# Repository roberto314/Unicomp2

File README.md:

# UNICOMP #

A modular 8-bit Computer able to recreate (nearly) every microcomputer of the mid 70s to early 80s 
in Hardware without FPGAs (although an FPGA can be added). Can also be used as a teaching tool for:

* VHDL or Verilog
* C
* RTOS (STM32F401 runs ChibiOS Link: https://www.chibios.org)
* Python
* bash and linux in general (Olimex board runs linux with fbterm and tmux)
* Harwaredesign
* Timing of CPUs
* maybe Assembler
* SPI and I2C Interfaces
* CPLDs and FPGAs

It is different from other designs because of these points:

* it uses a 3.3V only Bus,
* it uses fast RAM for chipselect with two byte resolution over the whole 1MB range,
* it uses one SRAM for RAM and ROM replacement (can be write writeprotected) with 512kB (1MB possible),
* it uses a clock generator chip (DS1085) - no more crystals to change,
* it is configureable via STM32 (RAM and ROM content, Clock frequency, chip select lines),
* it can program the CPLDs (only XC9572 and XC9536 tested) from the olimex board - no external programmer and no cables to connect,
* Board size is 100mm x 100mm - no backplane (like the PC/104 standard. Link: https://en.wikipedia.org/wiki/PC/104).
* and maybe most convenient: it can change RAM and ROM content on the fly without crashing the CPU. 
  For example starting the Apple I, going into Basic and uploading the program in about half a second is really nice.

Version 2.00

Unicomp plus Logic Analyzer:

### Unicomp modules ###

* Input board:
	- a simple board to connect the signals to a linux SBC like a Raspberry Pi or an Olimex A20
	- also generates the main clock with a DS1085 chip (in v2 this will be moved to the RAMROM board).
	- no CPLD

* CPU board:
	- can be any 8-bit CPU (6502, 6802, 6809, 68008, 6803, 8051,...)
	- a CPLD (XC9572) for clock generation and glue logic

6502 Board:

* Multi Serial boaŕd:
	- suggested chip select #0
	- two chip selects on board (second one not connected, but broken out)
	- can be used with the following serial interface chips: MC6850, MOS6551, MOS6552 or pin compatible
	- SRAM for address decoding

Multi Serial Board:

* Multi Parallel boaŕd:
	- suggested chip select #1
	- two chip selects on board
	- can be used with the following parallel interface chips: MC6820, MC6821, MOS6520, MOS6521, MOS6522, MOS6526, MOS8520, MOS6532 in the first slot
    - the first slot can additionally mimic a MOS6530
	- the second slot can accommodate a MOS6522 or pin compatible
    - SRAM for address decoding

* RAMROM board:
	- chip select fixed at #14 (for chipselect RAM) and #15 (rom content)
	- 512k of SRAM plus an extra RAM for address decoding
	- a STM32F401 'blackpill' board to fill the SRAMs with data over USB port from the SBC
	- USB shell on the STM32 to change ROM content on the fly
	- also configures the Address Range of all peripheral modules

* Prototype board:
	- empty board for prototyping
	- no CPLD
    - SRAM for address decoding

* MAX-II (EPM240) board:
	- CPLD plus Buffers

* self made module:
	- chip select can be any non-used line in the Range from 0 to 13.
	- size is 100mm x 100mm
	- there is the prototype board in the repository for the position of the connectors and also the labels (pinout)

### Configuration RAM ###

The configuration is done with 128kx8 fast ram on the peripheral boards. These will be configured from the STM32F401.
One bit is for one Output (of which there are two) and for two addresses (resolution for chipselect is 2 bytes).
The cs = 15 is for writing the main RAM, cs = 14 is the chip select for the RAMROM board.
The rest is free. With two chip select lines per board these are 28 lines.
One byte in the mapping ram has the following format:

| 7    | 6    | 5    | 4    | 3    | 2    | 1    | 0    | Bits       |
|------|------|------|------|------|------|------|------|------------|
| 7,6  | 5,4  | 3,2  | 1,0  | 7,6  | 5,4  | 3,2  | 1,0  | Address    |
| /CS0 | /CS0 | /CS0 | /CS0 | /CS1 | /CS1 | /CS1 | /CS1 | Peripheral |
| /CS  | /CS  | /CS  | /CS  | WP   | WP   | WP   | WP   | RAMROM     |

So 128k are good for 128kx8 Bytes of Addressspace (=1MByte)
The data gets transferred to the STM32 in compact form. Only the Start address, the chipselect and the bitmask (which is Low-active) for every addresses where someting changes are transferred.
A 0xFE for a bitmask means Peripheral chipselect /CS1 is active for two addresses. If the board is the RAMROM board the low nibble is Writeprotect (Hi-active).

A simple configuration block looks líke this:

    (RAM: 0-9FFF, ACIA0: A000-A001, ACIA1: A010-A011, ROM: C000-FFFF)

    00 00 00 0E 00  :  RAM
    00 A0 00 00 EF  :  ACIA0
    00 A0 02 FF FF  :  HOLE
    00 A0 10 00 FE  :  ACIA1
    00 A0 12 FF FF  :  HOLE
    00 C0 00 0E 0F  :  ROM
    01 00 00 FF FF  :  END
    00 00 00        :  noting further

### Working Recreations of old computers ###

| Name                     | prim. IO    | chips used                    | os                               | weblink                                                                 |
|--------------------------|-------------|-------------------------------|----------------------------------|-------------------------------------------------------------------------|
| Grant Searle 6502 board  | serial      | MOS6502, MC6850               | OSI Basic                        |Link: http://searle.x10host.com/6502/Simple6502.html                     |
| Daryl Rictor 6502 board  | serial      | MOS6502, R6551                | SBC-2 (monitor only)             |Link: https://sbc.rictor.org/info2.html                                  |
| Daryl Rictor 6502 board  | serial      | MOS6502, MC6850               | SBC-2 (monitor only)             |Link: https://sbc.rictor.org/info2.html                                  |
| SYM1                     | serial      | MOS6502, UM6532               | SYM1 ( +BASIC +RAE)              |Link: http://retro.hansotten.nl/6502-sbc/synertek-sym-ktm/sym-1/         |
| KIM1                     | serial      | MOS6502, UM6532               | KIM1                             |Link: http://retro.hansotten.nl/6502-sbc/kim-1-manuals-and-software/     |
| Apple I                  | serial      | MOS6502, MĆ6821 (plus Arduino)| Wozmon + BASIC                   |Link: http://retro.hansotten.nl/6502-sbc/apple-1/                        |
| Motorola MEK D2          | serial      | MC6802, MĆ6850                | newbug, xswtbug, mondeb          |Link: https://www.retrotechnology.com/restore/smithbug.html              |
| Motorola MEK D1          | serial      | MC6802, MĆ6821 (plus Arduino) | Mikbug                           |Link: https://www.retrotechnology.com/restore/smithbug.html              |
| Heathkit ET3400          | serial      | MC6802, MĆ6850                | MITS BASIC, TSC MicroBASIC,...   |Link: https://github.com/jefftranter                                     |
| SWTPC 6800               | serial      | MC6802, MĆ6821 (plus Arduino) | Mikbug                           |Link: https://deramp.com/swtpc.com/                                      |
| SWTPC 6800               | serial      | MC6802, MĆ6850                | SWTBUG, SWTBUGA, Mondeb, xSWTBUG |Link: https://deramp.com/swtpc.com/                                      |
| DREAM 6800               | BAS (Video) | MC6802, MAX-II                | DREAM operating System (Chip8)   |Link: http://www.mjbauer.biz/DREAM6800.htm                               |
| HD6303 Board (Eric Klaus)| serial      | HD6303                        | Monitor +BASIC                   |Link: https://sites.google.com/site/ericmklaus/projects-1/hd6303cpuboard |
| MC3 Computer             | serial      | HD6303                        | Monitor                          |Link: https://www.waveguide.se/?article=mc3-a-diy-8-bit-computer         |
| Psion Organizer I        | LCD         | HD6303                        | Psion OS                         |Link: https://www.jaapsch.net/psion/index.htm                            |

### linux single board computer (SBC) ###

I uses an olimex A20 SBC (olinuxino A20) which has a lot of peripherals (4x UART, 2x SPI, 2x I2C, a lot of GPIOs, SATA, 2x SDCARD, VGA, HDMI, LAN,...)
and it is open hardware. The board is connected with three 40 pin cables (like old IDE cables) plus two 10 pin cables to the input board.

To access all the peripherals i use python with the pyA20 library here: https://pypi.org/project/pyA20/   
The debian image (bullseye minimal) can be found at: http://images.olimex.com/release/a20/   
To configure the image after downloading there are helper scripts in the unicomp folder under: olimex Board/config 
I use fbterm and tmux for a nice terminal output. Here are some pictures:   
tmux main window:

tmux serial window:

### python helper scripts ###

-- all scripts have to be executed with sudo bacause of direct hardware access!

* set_reset.py [0,1,xx]
	- sets the reset line high or low (low = active)
	- if value is anything other than 0 or 1 then a reset of approx. 10mS will be performed.

* UC_check_jtag.sh
	- looks for devices (CPLDs) in the JTAG chain.

* UC_write_cpld.sh [0..?] [.jed file]
	- writes the .jed file to the selected devices
	- Example: sudo UC_write_cpld 0 filename.jed - writes .jed file to cpld zero

* Prepare new SD-Card:
    - copy image to sd-card:
    sudo dd if=A20-OLinuXino-bullseye-minimal-20230515-130040.img of=/dev/sdb bs=1k status=progress
    - start olimex and login with 'olimex/olimex'
    - change password with: 'sudo passwd olimex' to something shorter like 'olim'
    - alternatively: delete passwird: 'sudo passwd -d olimex'
    - make update: 'sudo apt update && sudo apt upgrade'
    - install minimal components: 'sudo apt install git mc'
    - clone github repository: 'git clone https://github.com/roberto314/Unicomp2.git'
    - open midnight commander: 'mc'
    - navigate into Unicomp2/olimex_board/config
    - Run script: 'install_software.sh'
    - Run script: 'copy_files.sh'
    - restart

### CPLD programming ###

* compiling the vhdl (or verilog) code must be done on a computer with the Xilinx ISE 14.7 toolchain installed.
 Link: https://www.xilinx.com/support/download/index.html/content/xilinx/en/downloadNav/vivado-design-tools/archive-ise.html

* compiling itself can be done inside ISE or with the supplied makefile (look inside the bord directory in cpld firmware)

* a simple **make** will compile the firmware and a **make transfer** will transfer the file to the sbc (if you changed the ip address to your address inside the makefile and the path inside project.cfg)

* on the sbc in the work folder one can find the .jed file. For programming type: **UC_write_cpld [JTAG-position] [filename.jed]**

### Used Software and OS ###

* Linux Mint (20.3 cinnamon) (Link: https://linuxmint.com/)
* Sublime Text 3 (Link: https://www.sublimetext.com/)
* 010 Editor (Hex Editor) (Link: https://www.sweetscape.com/010editor/)
* Chibi Studio 20 (IDE for ChibiOS) (Link: https://www.chibios.org/dokuwiki/doku.php?id=chibios:products:chibistudio:start)
* Wavedrom (2.9.1) (Link: https://wavedrom.com/)
* Pulseview (0.5.0-nightly Appimaage) (Part of sigrok) (Link: https://sigrok.org/wiki/PulseView)
* Logisim-Evolution (3.8.0) (Link: https://github.com/logisim-evolution/logisim-evolution)
* Quartus (13.0.1 Build232 Web Edition - 64 Bit) for MAX-II
* Xilinx ISE (14.7 - 64 Bit) for XC9572

### Used Hardware ###

* Oscilloscope: Rigol DS1054Z (4 channel)
* Logic Analyzer: Hantek 4032L (32 channel)

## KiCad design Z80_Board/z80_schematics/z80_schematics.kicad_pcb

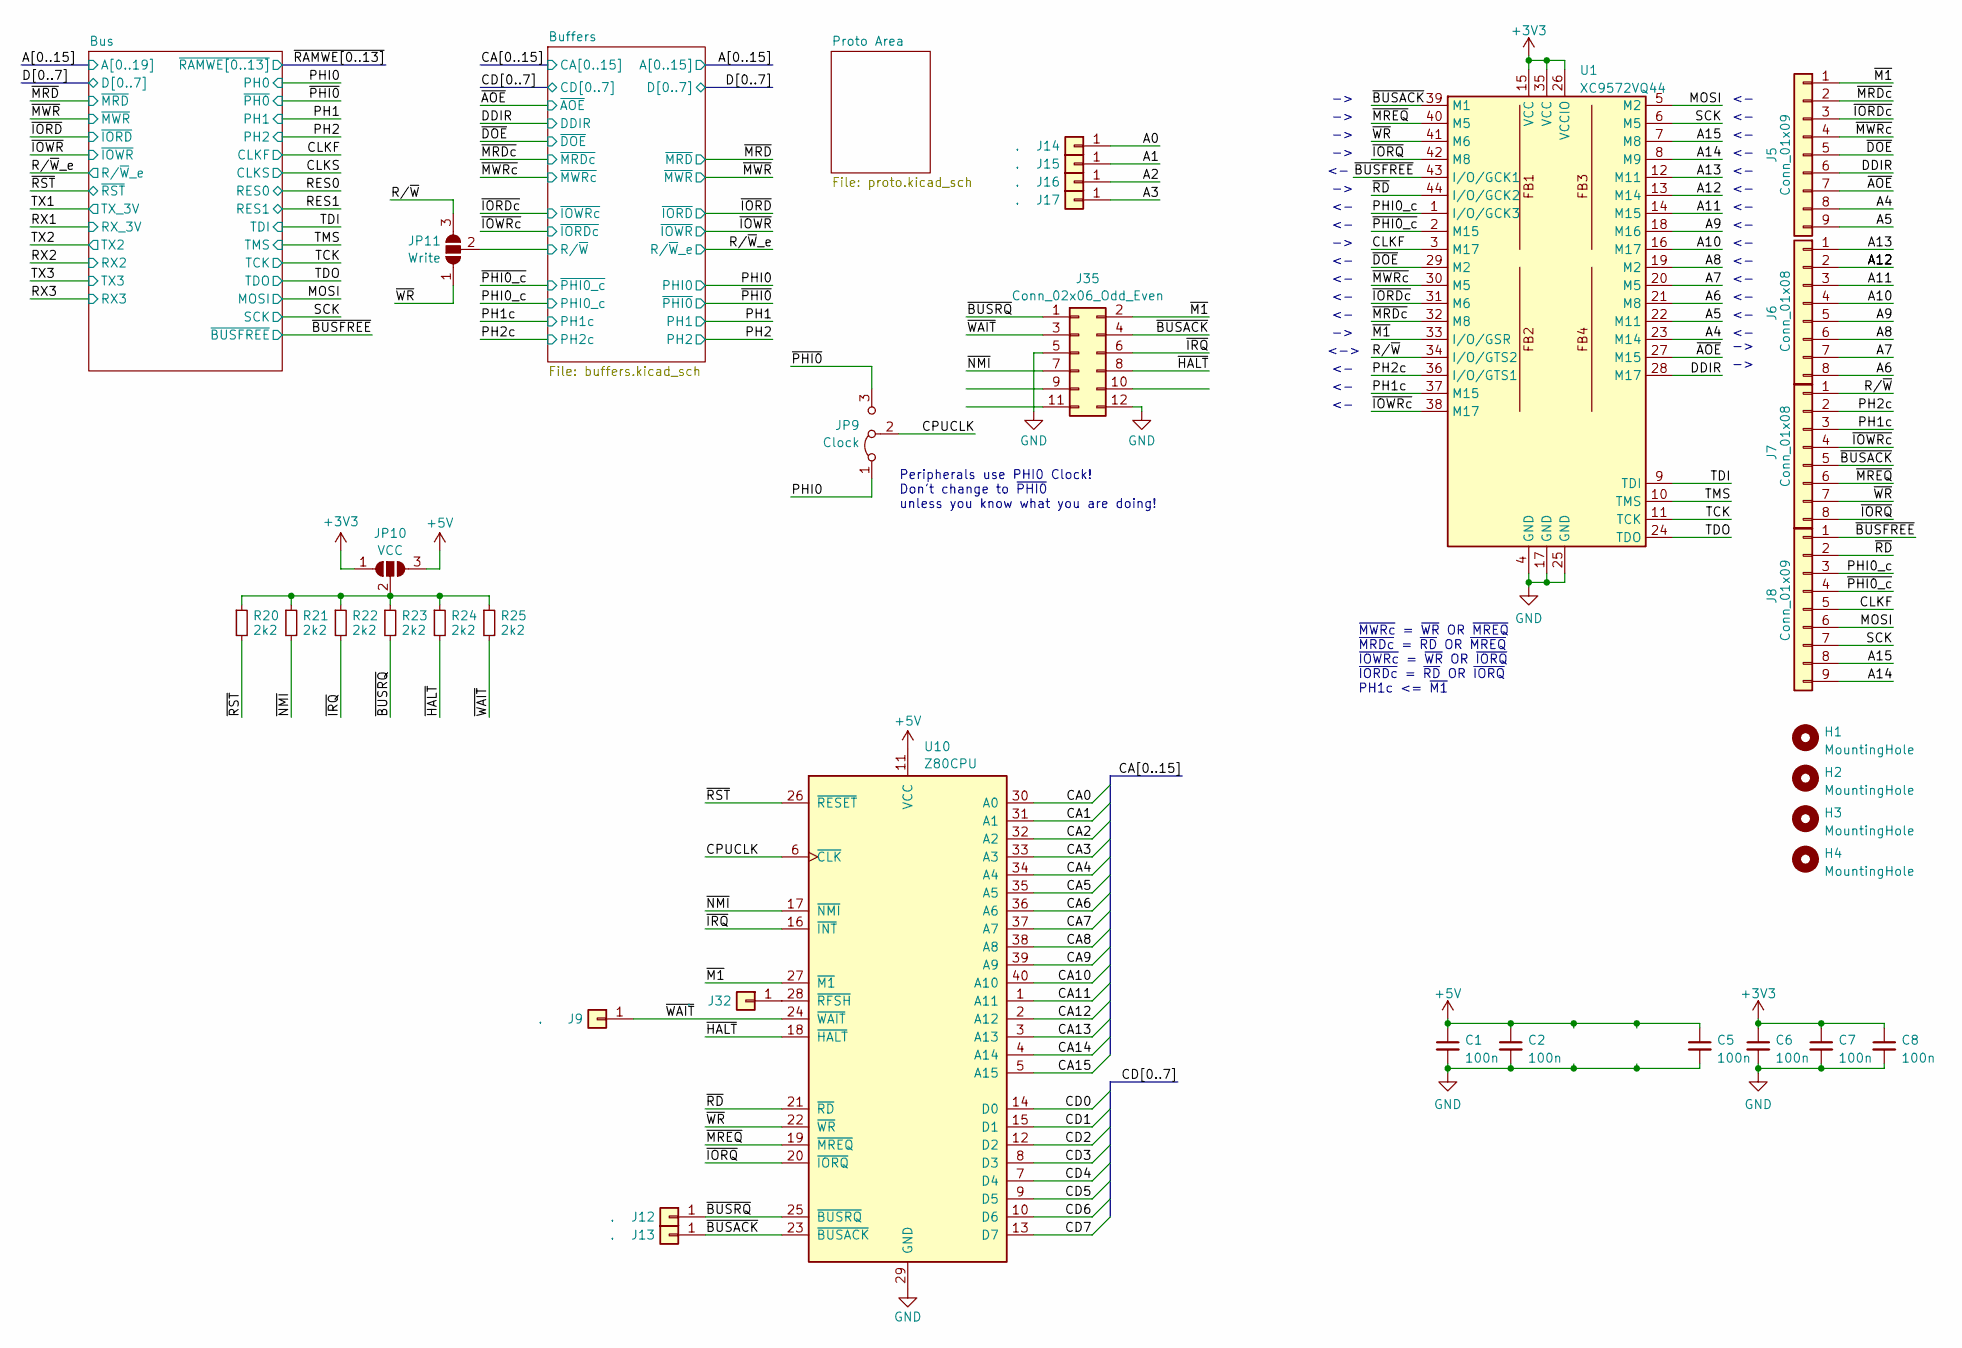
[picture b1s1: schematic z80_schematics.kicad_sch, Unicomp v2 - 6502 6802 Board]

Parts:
C1, C2, C5, C6, C7, C8: 100n; C_1206_3216Metric
H1, H2, H3, H4: MountingHole; MountingHole_3.2mm_M3
J5, J8: Conn_01x09; PinHeader_1x09_P2.54mm_Vertical
J6, J7: Conn_01x08; PinHeader_1x08_P2.54mm_Vertical
J9, J12, J13, J14, J15, J16, J17, J32: .; PinHeader_1x01_P2.00mm_Vertical
J35: Conn_02x06_Odd_Even; PinHeader_2x06_P2.54mm_Horizontal
JP9: Clock; SolderJumper-3_P1.3mm_Bridged12_RoundedPad1.0x1.5mm
JP10: VCC; SolderJumper-3_P1.3mm_Open_RoundedPad1.0x1.5mm_NumberLabels
JP11: Write; SolderJumper-3_P1.3mm_Open_RoundedPad1.0x1.5mm_NumberLabels
R20, R21, R22, R23, R24, R25: 2k2; R_1206_3216Metric_Pad1.30x1.75mm_HandSolder
U1: XC9572VQ44; TQFP-44_10x10mm_P0.8mm
U10: Z80CPU; DIP-40_W15.24mm_Socket_LongPads

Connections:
+3V3: C6.1, C7.1, C8.1, JP10.1 (A), U1.15 (VCC), U1.26 (VCCIO), U1.35 (VCC); also elsewhere on the board
+5V: C1.1, C2.1, C5.1, JP10.3 (B), U10.11 (VCC); also elsewhere on the board
/A0: J14.1; also elsewhere on the board
/A1: J15.1; also elsewhere on the board
/A2: J16.1; also elsewhere on the board
/A3: J17.1; also elsewhere on the board
/A4: J5.8, U1.23 (M14); also elsewhere on the board
/A5: J5.9, U1.22 (M11); also elsewhere on the board
/A6: J6.8, U1.21 (M8); also elsewhere on the board
/A7: J6.7, U1.20 (M5); also elsewhere on the board
/A8: J6.6, U1.19 (M2); also elsewhere on the board
/A9: J6.5, U1.18 (M16); also elsewhere on the board
/A10: J6.4, U1.16 (M17); also elsewhere on the board
/A11: J6.3, U1.14 (M15); also elsewhere on the board
/A12: J6.2, U1.13 (M14); also elsewhere on the board
/A13: J6.1, U1.12 (M11); also elsewhere on the board
/A14: J8.9, U1.8 (M9); also elsewhere on the board
/A15: J8.8, U1.7 (M8); also elsewhere on the board
/Buffers/R/~W: JP11.2 (C); also elsewhere on the board
/CA0: U10.30 (A0); also elsewhere on the board
/CA1: U10.31 (A1); also elsewhere on the board
/CA2: U10.32 (A2); also elsewhere on the board
/CA3: U10.33 (A3); also elsewhere on the board
/CA4: U10.34 (A4); also elsewhere on the board
/CA5: U10.35 (A5); also elsewhere on the board
/CA6: U10.36 (A6); also elsewhere on the board
/CA7: U10.37 (A7); also elsewhere on the board
/CA8: U10.38 (A8); also elsewhere on the board
/CA9: U10.39 (A9); also elsewhere on the board
/CA10: U10.40 (A10); also elsewhere on the board
/CA11: U10.1 (A11); also elsewhere on the board
/CA12: U10.2 (A12); also elsewhere on the board
/CA13: U10.3 (A13); also elsewhere on the board
/CA14: U10.4 (A14); also elsewhere on the board
/CA15: U10.5 (A15); also elsewhere on the board
/CD0: U10.14 (D0); also elsewhere on the board
/CD1: U10.15 (D1); also elsewhere on the board
/CD2: U10.12 (D2); also elsewhere on the board
/CD3: U10.8 (D3); also elsewhere on the board
/CD4: U10.7 (D4); also elsewhere on the board
/CD5: U10.9 (D5); also elsewhere on the board
/CD6: U10.10 (D6); also elsewhere on the board
/CD7: U10.13 (D7); also elsewhere on the board
/CLKF: J8.5, U1.3 (M17); also elsewhere on the board
/CPUCLK: JP9.2 (C), U10.6 (~CLK)
/DDIR: J5.6, U1.28 (M17); also elsewhere on the board
/MOSI: J8.6, U1.5 (M2); also elsewhere on the board
/PH1c: J7.3, U1.37 (M15); also elsewhere on the board
/PH2c: J7.2, U1.36 (I/O/GTS1); also elsewhere on the board
/PHI0: JP9.1 (A); also elsewhere on the board
/PHI0_c: J8.3, U1.1 (I/O/GCK3); also elsewhere on the board
/R/~W: J7.1, JP11.3 (B), U1.34 (I/O/GTS2)
/SCK: J8.7, U1.6 (M5); also elsewhere on the board
/TCK: U1.11 (TCK); also elsewhere on the board
/TDI: U1.9 (TDI); also elsewhere on the board
/TDO: U1.24 (TDO); also elsewhere on the board
/TMS: U1.10 (TMS); also elsewhere on the board
/~AOE: J5.7, U1.27 (M15); also elsewhere on the board
/~BUSACK: J7.5, J13.1, J35.4, U1.39 (M1), U10.23 (~BUSACK)
/~BUSFREE: J8.1, U1.43 (I/O/GCK1); also elsewhere on the board
/~BUSRQ: J12.1, J35.1, R23.2, U10.25 (~BUSRQ)
/~DOE: J5.5, U1.29 (M2); also elsewhere on the board
/~HALT: J35.8, R24.2, U10.18 (~HALT)
/~IORDc: J5.3, U1.31 (M6); also elsewhere on the board
/~IORQ: J7.8, U1.42 (M8), U10.20 (~IORQ)
/~IOWRc: J7.4, U1.38 (M17); also elsewhere on the board
/~IRQ: J35.6, R22.2, U10.16 (~INT)
/~M1: J5.1, J35.2, U1.33 (I/O/GSR), U10.27 (~M1)
/~MRDc: J5.2, U1.32 (M8); also elsewhere on the board
/~MREQ: J7.6, U1.40 (M5), U10.19 (~MREQ)
/~MWRc: J5.4, U1.30 (M5); also elsewhere on the board
/~NMI: J35.7, R21.2, U10.17 (~NMI)
/~PHI0_c: J8.4, U1.2 (M15); also elsewhere on the board
/~PHI0: JP9.3 (B); also elsewhere on the board
/~RD: J8.2, U1.44 (I/O/GCK2), U10.21 (~RD)
/~RST: R20.2, U10.26 (~RESET); also elsewhere on the board
/~WAIT: J9.1, J35.3, R25.2, U10.24 (~WAIT)
/~WR: J7.7, JP11.1 (A), U1.41 (M6), U10.22 (~WR)
GND: C1.2, C2.2, C5.2, C6.2, C7.2, C8.2, J35.5, J35.12, U1.4 (GND), U1.17 (GND), U1.25 (GND), U10.29 (GND); also elsewhere on the board
unnamed: J32.1, U10.28 (~RFSH)
unnamed: JP10.2 (C), R20.1, R21.1, R22.1, R23.1, R24.1, R25.1

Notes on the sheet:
<->
~{MWRc} = ~{WR} OR ~{MREQ} ~{MRDc} = ~{RD} OR ~{MREQ} ~{IOWRc} = ~{WR} OR ~{IORQ} ~{IORDc} = ~{RD} OR ~{IORQ} PH1c <= ~{M1}
Peripherals use PHI0 Clock! Don't change to ~{PHI0} unless you know what you are doing!

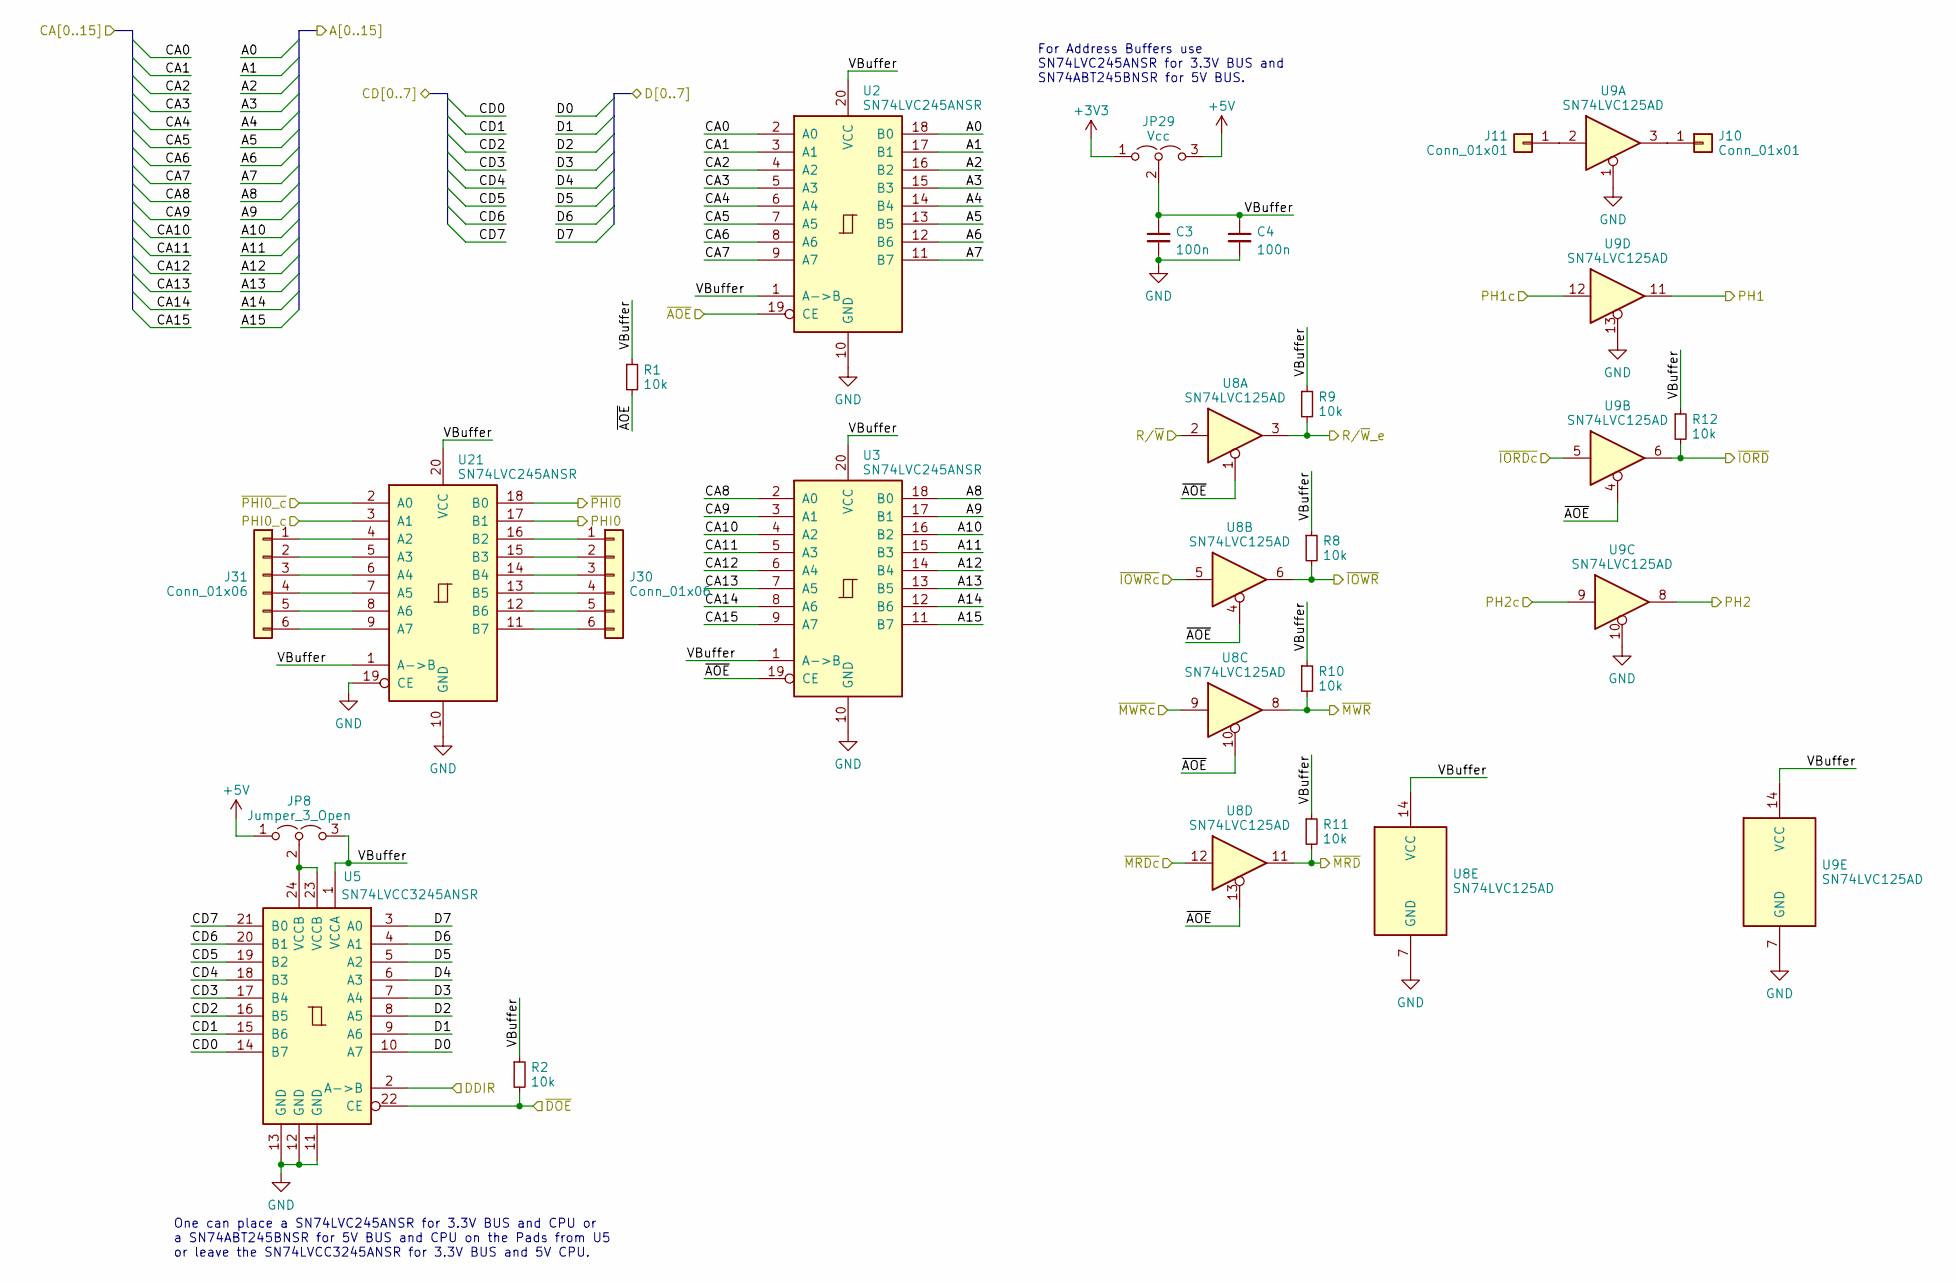
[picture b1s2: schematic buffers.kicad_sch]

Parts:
C3, C4: 100n; C_1206_3216Metric
J10, J11: Conn_01x01; PinHeader_1x01_P1.27mm_Vertical
J30, J31: Conn_01x06; PinHeader_1x06_P1.27mm_Vertical
JP8: Jumper_3_Open; SolderJumper-3_P1.3mm_Open_Pad1.0x1.5mm_NumberLabels
JP29: Vcc; SolderJumper-3_P1.3mm_Open_RoundedPad1.0x1.5mm_NumberLabels
R1, R2, R8, R9, R10, R11, R12: 10k; R_1206_3216Metric_Pad1.30x1.75mm_HandSolder
U2, U3, U21: SN74LVC245ANSR; SO-20_5.3x12.6mm_P1.27mm
U5: SN74LVCC3245ANSR; SO-24_5.3x15mm_P1.27mm
U8, U9: SN74LVC125AD; SOIC-14_3.9x8.7mm_P1.27mm

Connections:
+3V3: JP29.1 (A); also elsewhere on the board
+5V: JP8.1 (A), JP29.3 (B); also elsewhere on the board
/A0: U2.18 (B0); also elsewhere on the board
/A1: U2.17 (B1); also elsewhere on the board
/A2: U2.16 (B2); also elsewhere on the board
/A3: U2.15 (B3); also elsewhere on the board
/A4: U2.14 (B4); also elsewhere on the board
/A5: U2.13 (B5); also elsewhere on the board
/A6: U2.12 (B6); also elsewhere on the board
/A7: U2.11 (B7); also elsewhere on the board
/A8: U3.18 (B0); also elsewhere on the board
/A9: U3.17 (B1); also elsewhere on the board
/A10: U3.16 (B2); also elsewhere on the board
/A11: U3.15 (B3); also elsewhere on the board
/A12: U3.14 (B4); also elsewhere on the board
/A13: U3.13 (B5); also elsewhere on the board
/A14: U3.12 (B6); also elsewhere on the board
/A15: U3.11 (B7); also elsewhere on the board
/Buffers/R/~W: U8.2; also elsewhere on the board
/Buffers/VBuffer: C3.1, C4.1, JP8.3 (B), JP29.2 (C), R1.1, R2.1, R8.1, R9.1, R10.1, R11.1, R12.1, U2.1 (A->B), U2.20 (VCC), U3.1 (A->B), U3.20 (VCC), U5.1 (VCCA), U8.14 (VCC), U9.14 (VCC), U21.1 (A->B), U21.20 (VCC)
/CA0: U2.2 (A0); also elsewhere on the board
/CA1: U2.3 (A1); also elsewhere on the board
/CA2: U2.4 (A2); also elsewhere on the board
/CA3: U2.5 (A3); also elsewhere on the board
/CA4: U2.6 (A4); also elsewhere on the board
/CA5: U2.7 (A5); also elsewhere on the board
/CA6: U2.8 (A6); also elsewhere on the board
/CA7: U2.9 (A7); also elsewhere on the board
/CA8: U3.2 (A0); also elsewhere on the board
/CA9: U3.3 (A1); also elsewhere on the board
/CA10: U3.4 (A2); also elsewhere on the board
/CA11: U3.5 (A3); also elsewhere on the board
/CA12: U3.6 (A4); also elsewhere on the board
/CA13: U3.7 (A5); also elsewhere on the board
/CA14: U3.8 (A6); also elsewhere on the board
/CA15: U3.9 (A7); also elsewhere on the board
/CD0: U5.14 (B7); also elsewhere on the board
/CD1: U5.15 (B6); also elsewhere on the board
/CD2: U5.16 (B5); also elsewhere on the board
/CD3: U5.17 (B4); also elsewhere on the board
/CD4: U5.18 (B3); also elsewhere on the board
/CD5: U5.19 (B2); also elsewhere on the board
/CD6: U5.20 (B1); also elsewhere on the board
/CD7: U5.21 (B0); also elsewhere on the board
/D0: U5.10 (A7); also elsewhere on the board
/D1: U5.9 (A6); also elsewhere on the board
/D2: U5.8 (A5); also elsewhere on the board
/D3: U5.7 (A4); also elsewhere on the board
/D4: U5.6 (A3); also elsewhere on the board
/D5: U5.5 (A2); also elsewhere on the board
/D6: U5.4 (A1); also elsewhere on the board
/D7: U5.3 (A0); also elsewhere on the board
/DDIR: U5.2 (A->B); also elsewhere on the board
/PH1: U9.11; also elsewhere on the board
/PH1c: U9.12; also elsewhere on the board
/PH2: U9.8; also elsewhere on the board
/PH2c: U9.9; also elsewhere on the board
/PHI0: U21.17 (B1); also elsewhere on the board
/PHI0_c: U21.3 (A1); also elsewhere on the board
/R/~W_e: R9.2, U8.3; also elsewhere on the board
/~AOE: R1.2, U2.19 (CE), U3.19 (CE), U8.1, U8.4, U8.10, U8.13, U9.4; also elsewhere on the board
/~DOE: R2.2, U5.22 (CE); also elsewhere on the board
/~IORDc: U8.5; also elsewhere on the board
/~IORD: R12.2, U9.6; also elsewhere on the board
/~IOWRc: U9.5; also elsewhere on the board
/~IOWR: R8.2, U8.6; also elsewhere on the board
/~MRDc: U8.12; also elsewhere on the board
/~MRD: R11.2, U8.11; also elsewhere on the board
/~MWRc: U8.9; also elsewhere on the board
/~MWR: R10.2, U8.8; also elsewhere on the board
/~PHI0_c: U21.2 (A0); also elsewhere on the board
/~PHI0: U21.18 (B0); also elsewhere on the board
GND: C3.2, C4.2, U2.10 (GND), U3.10 (GND), U5.11 (GND), U5.12 (GND), U5.13 (GND), U8.7 (GND), U9.1, U9.7 (GND), U9.10, U9.13, U21.10 (GND), U21.19 (CE); also elsewhere on the board
unnamed: J10.1, U9.3
unnamed: J11.1, U9.2
unnamed: J30.1, U21.16 (B2)
unnamed: J30.2, U21.15 (B3)
unnamed: J30.3, U21.14 (B4)
unnamed: J30.4, U21.13 (B5)
unnamed: J30.5, U21.12 (B6)
unnamed: J30.6, U21.11 (B7)
unnamed: J31.1, U21.4 (A2)
unnamed: J31.2, U21.5 (A3)
unnamed: J31.3, U21.6 (A4)
unnamed: J31.4, U21.7 (A5)
unnamed: J31.5, U21.8 (A6)
unnamed: J31.6, U21.9 (A7)
unnamed: JP8.2 (C), U5.23 (VCCB), U5.24 (VCCB)

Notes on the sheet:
One can place a SN74LVC245ANSR for 3.3V BUS and CPU or a SN74ABT245BNSR for 5V BUS and CPU on the Pads from U5 or leave the SN74LVCC3245ANSR for 3.3V BUS and 5V CPU.
For Address Buffers use SN74LVC245ANSR for 3.3V BUS and SN74ABT245BNSR for 5V BUS.

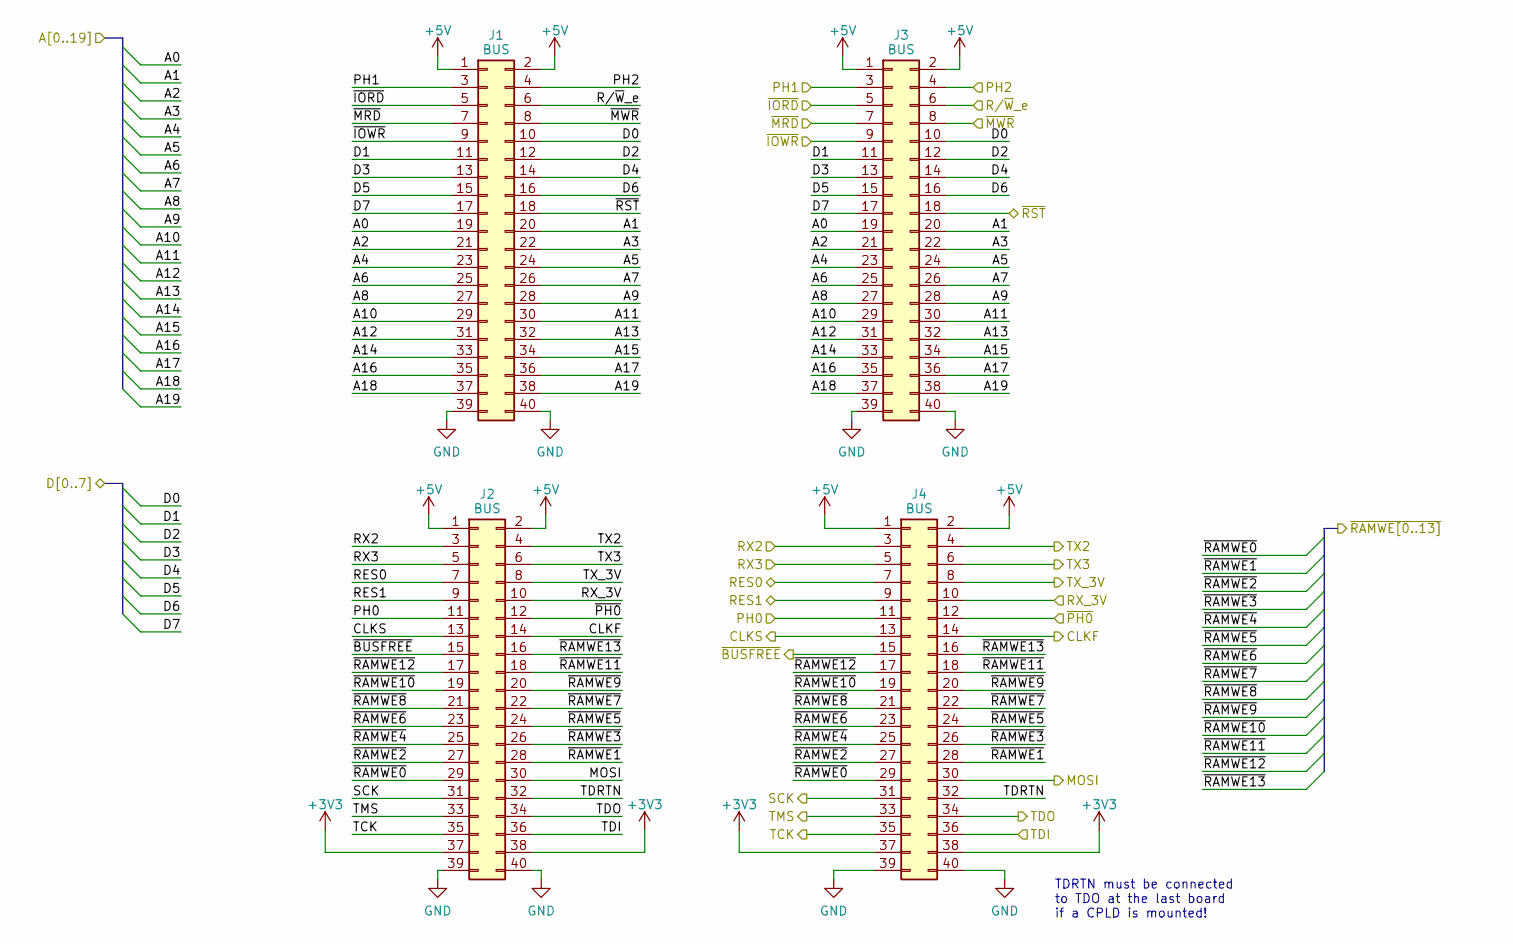
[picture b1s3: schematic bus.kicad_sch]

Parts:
J1, J2, J3, J4: BUS; PinSocket_2x20_P2.54mm_Vertical

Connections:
+3V3: J2.37, J2.38, J4.37, J4.38; also elsewhere on the board
+5V: J1.1, J1.2, J2.1, J2.2, J3.1, J3.2, J4.1, J4.2; also elsewhere on the board
/A0: J1.19, J3.19; also elsewhere on the board
/A1: J1.20, J3.20; also elsewhere on the board
/A2: J1.21, J3.21; also elsewhere on the board
/A3: J1.22, J3.22; also elsewhere on the board
/A4: J1.23, J3.23; also elsewhere on the board
/A5: J1.24, J3.24; also elsewhere on the board
/A6: J1.25, J3.25; also elsewhere on the board
/A7: J1.26, J3.26; also elsewhere on the board
/A8: J1.27, J3.27; also elsewhere on the board
/A9: J1.28, J3.28; also elsewhere on the board
/A10: J1.29, J3.29; also elsewhere on the board
/A11: J1.30, J3.30; also elsewhere on the board
/A12: J1.31, J3.31; also elsewhere on the board
/A13: J1.32, J3.32; also elsewhere on the board
/A14: J1.33, J3.33; also elsewhere on the board
/A15: J1.34, J3.34; also elsewhere on the board
/Bus/A16: J1.35, J3.35
/Bus/A17: J1.36, J3.36
/Bus/A18: J1.37, J3.37
/Bus/A19: J1.38, J3.38
/Bus/TDRTN: J2.32, J4.32
/CLKF: J2.14, J4.14; also elsewhere on the board
/CLKS: J2.13, J4.13
/D0: J1.10, J3.10; also elsewhere on the board
/D1: J1.11, J3.11; also elsewhere on the board
/D2: J1.12, J3.12; also elsewhere on the board
/D3: J1.13, J3.13; also elsewhere on the board
/D4: J1.14, J3.14; also elsewhere on the board
/D5: J1.15, J3.15; also elsewhere on the board
/D6: J1.16, J3.16; also elsewhere on the board
/D7: J1.17, J3.17; also elsewhere on the board
/MOSI: J2.30, J4.30; also elsewhere on the board
/PH1: J1.3, J3.3; also elsewhere on the board
/PH2: J1.4, J3.4; also elsewhere on the board
/PHI0: J2.11, J4.11; also elsewhere on the board
/RES0: J2.7, J4.7
/RES1: J2.9, J4.9
/RX1: J2.10, J4.10
/RX2: J2.3, J4.3
/RX3: J2.5, J4.5
/R/~W_e: J1.6, J3.6; also elsewhere on the board
/SCK: J2.31, J4.31; also elsewhere on the board
/TCK: J2.35, J4.35; also elsewhere on the board
/TDI: J2.36, J4.36; also elsewhere on the board
/TDO: J2.34, J4.34; also elsewhere on the board
/TMS: J2.33, J4.33; also elsewhere on the board
/TX1: J2.8, J4.8
/TX2: J2.4, J4.4
/TX3: J2.6, J4.6
/~BUSFREE: J2.15, J4.15; also elsewhere on the board
/~IORD: J1.5, J3.5; also elsewhere on the board
/~IOWR: J1.9, J3.9; also elsewhere on the board
/~MRD: J1.7, J3.7; also elsewhere on the board
/~MWR: J1.8, J3.8; also elsewhere on the board
/~PHI0: J2.12, J4.12; also elsewhere on the board
/~RAMWE0: J2.29, J4.29
/~RAMWE1: J2.28, J4.28
/~RAMWE2: J2.27, J4.27
/~RAMWE3: J2.26, J4.26
/~RAMWE4: J2.25, J4.25
/~RAMWE5: J2.24, J4.24
/~RAMWE6: J2.23, J4.23
/~RAMWE7: J2.22, J4.22
/~RAMWE8: J2.21, J4.21
/~RAMWE9: J2.20, J4.20
/~RAMWE10: J2.19, J4.19
/~RAMWE11: J2.18, J4.18
/~RAMWE12: J2.17, J4.17
/~RAMWE13: J2.16, J4.16
/~RST: J1.18, J3.18; also elsewhere on the board
GND: J1.39, J1.40, J2.39, J2.40, J3.39, J3.40, J4.39, J4.40; also elsewhere on the board

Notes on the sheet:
TDRTN must be connected to TDO at the last board if a CPLD is mounted!

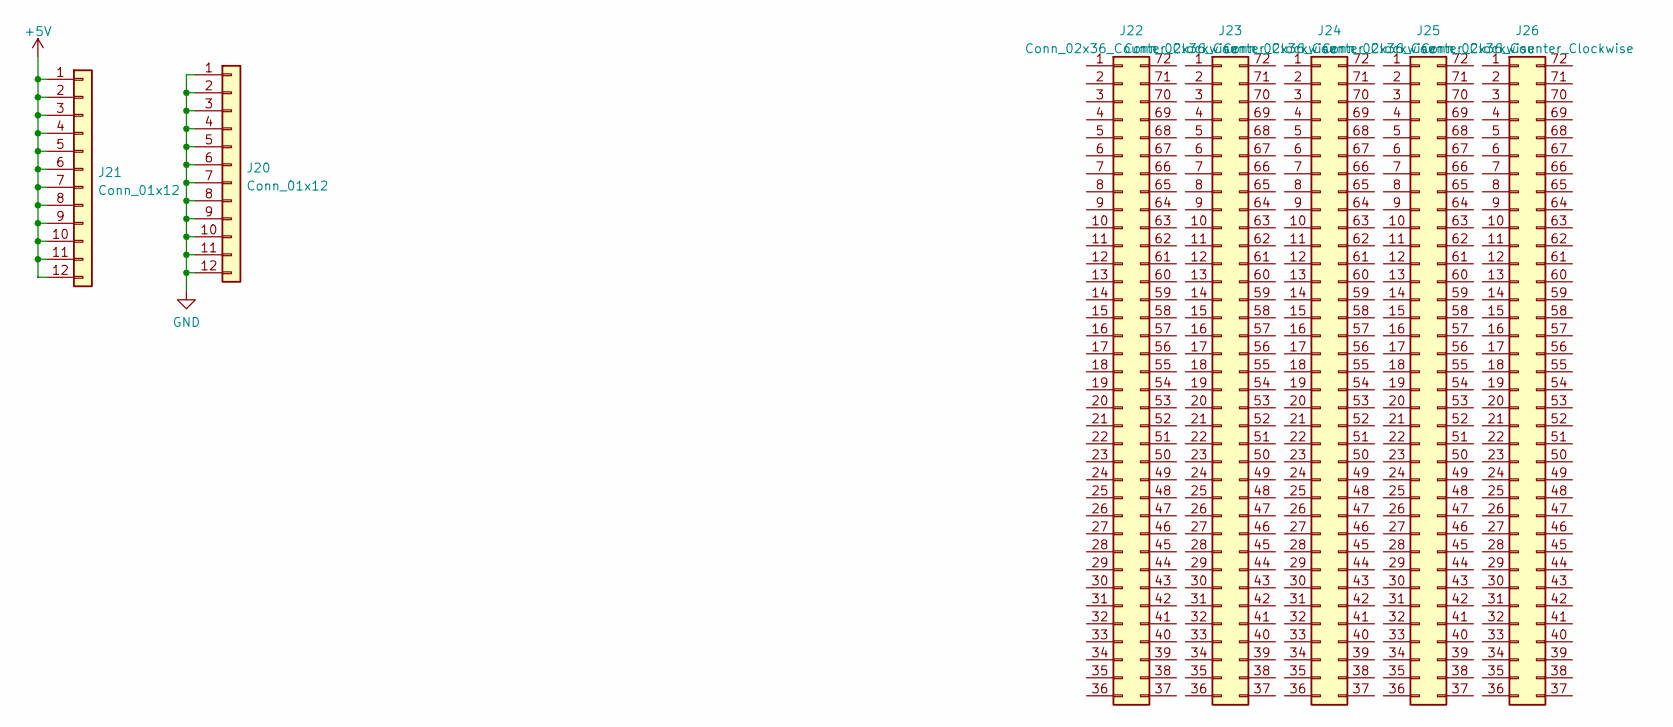
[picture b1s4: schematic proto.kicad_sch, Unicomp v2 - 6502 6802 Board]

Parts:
J20, J21: Conn_01x12; PinHeader_1x12_P2.54mm_Vertical
J22, J23, J24, J25, J26: Conn_02x36_Counter_Clockwise; Proto_2x36

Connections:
+5V: J21.1, J21.2, J21.3, J21.4, J21.5, J21.6, J21.7, J21.8, J21.9, J21.10, J21.11, J21.12; also elsewhere on the board
GND: J20.1, J20.2, J20.3, J20.4, J20.5, J20.6, J20.7, J20.8, J20.9, J20.10, J20.11, J20.12; also elsewhere on the board

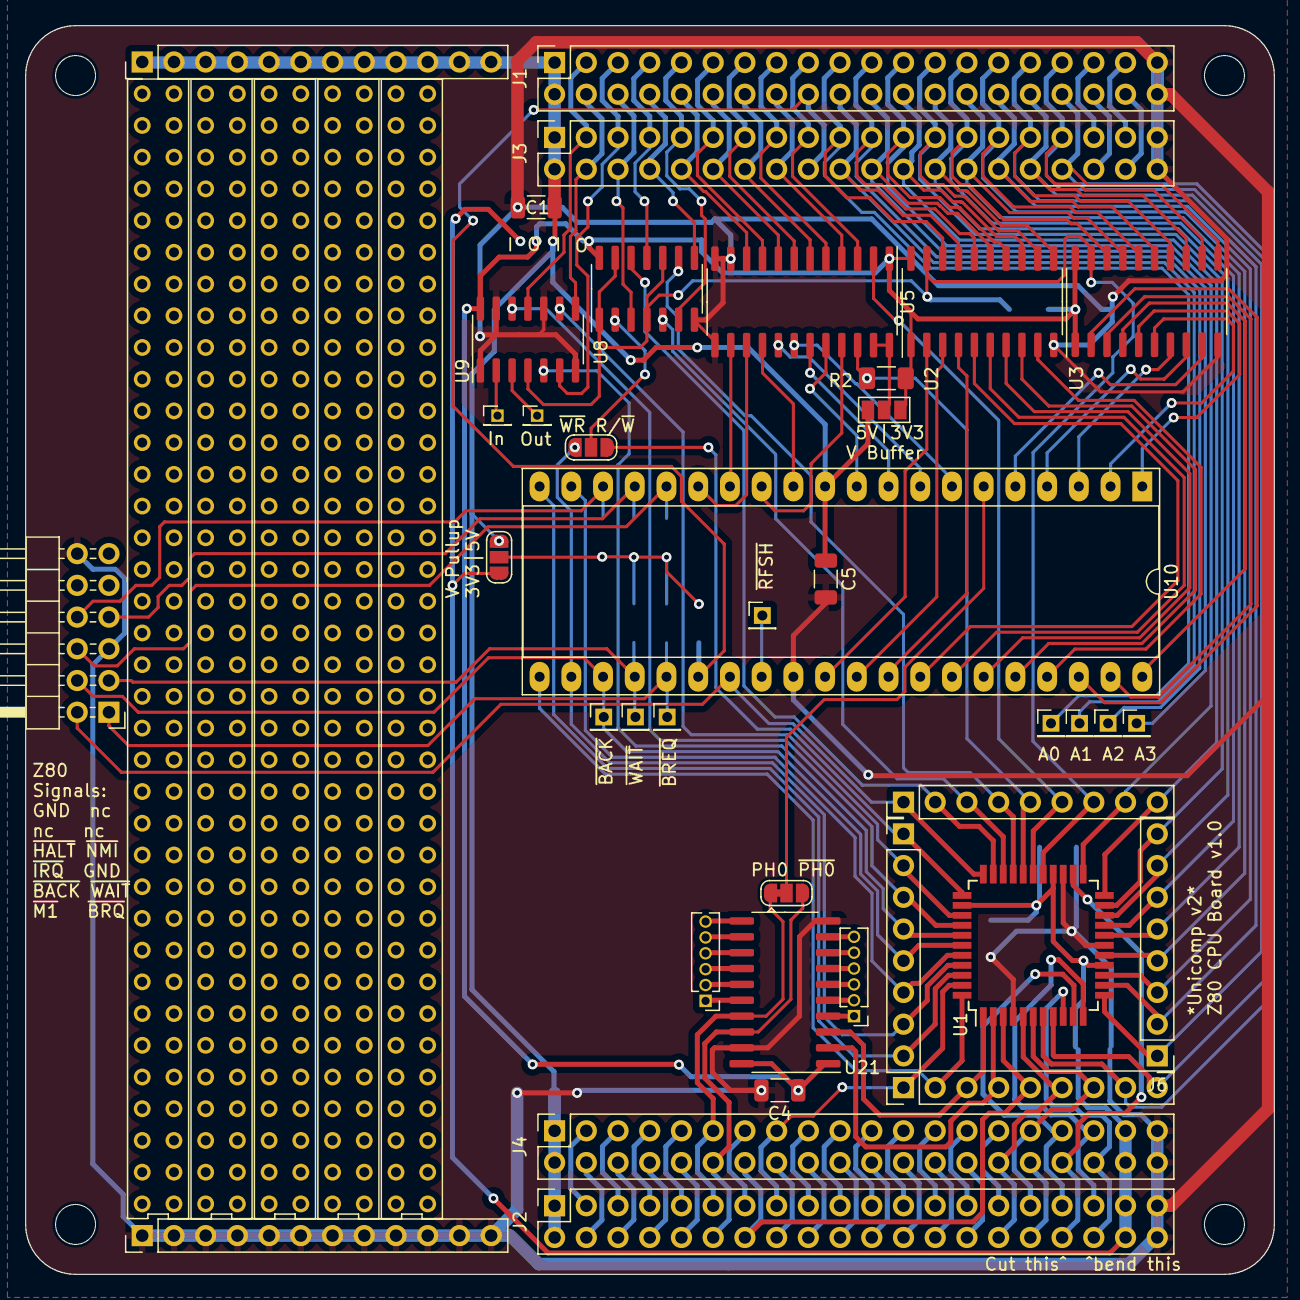
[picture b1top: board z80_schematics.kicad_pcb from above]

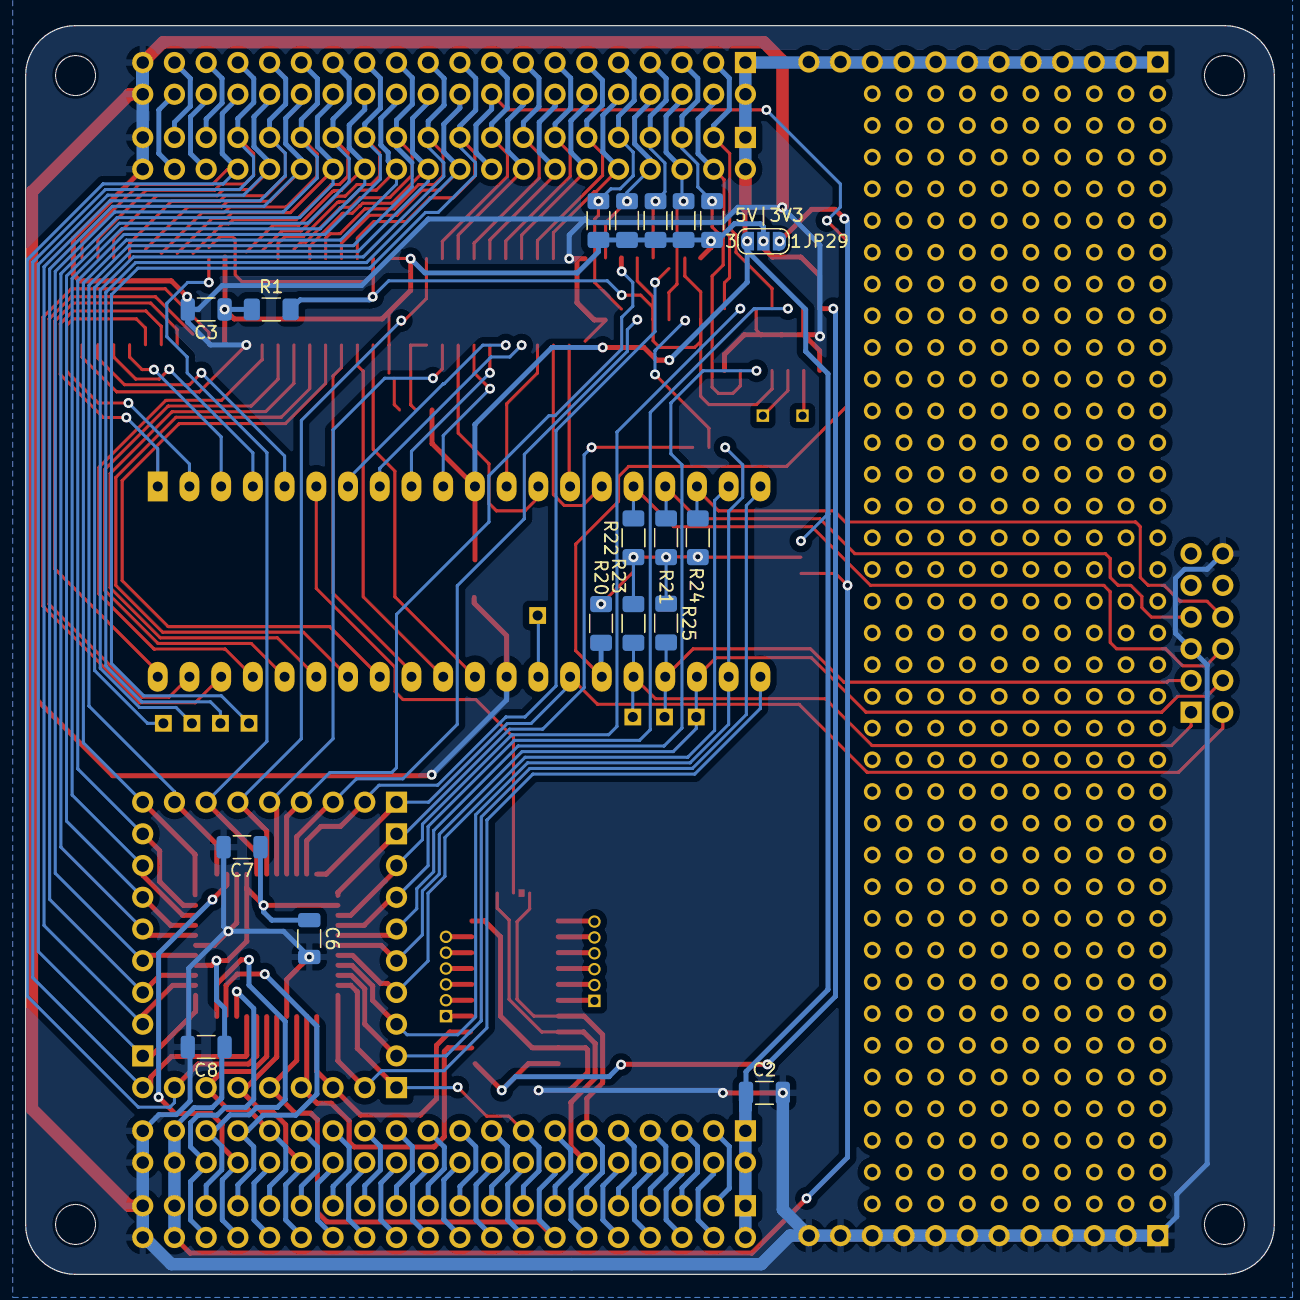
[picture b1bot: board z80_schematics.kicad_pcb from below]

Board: 2 copper layers, 100.0 x 100.0 mm, 66 parts (18 on the bottom side), 140 nets.
